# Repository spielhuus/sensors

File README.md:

# IoT Sensors

In this Project some IoT Sensors and actors are created. The goal is it to build low energy and cost efficient modules Depending

Various IoT Sensors using Wi-Fi or Lora.

# Sensor Projects

## Attiny/LoraWan Temperature and CO2 Sensor 

## Attmega328 Multi Sensor Board

The Atmega 328 Board has connector to different sesnsors. The collected data is uloaded to the things network.

Sensors
- BME280
- 

# Datasheets

- [AVR Microcontroller Hardware Design Considerations](https://www.microchip.com/wwwAppNotes/AppNotes.aspx?appnote=en591472)
- [BME280](https://ae-bst.resource.bosch.com/media/_tech/media/datasheets/BST-BME280_DS002.pdf)
- [CCS811]https://ams.com/documents/20143/36005/CCS811_AN000368_2-00.pdf/eca2b181-2937-ca92-65b5-9b43550bb20f)

# Links

- https://www.mikrocontroller.net/articles/AVR-Tutorial
- https://github.com/ClemensRiederer/TinyLoRa-BME280_v1.1
- https://learn.sparkfun.com/tutorials/ccs811-air-quality-breakout-hookup-guide
- http://www.iot-lab.org/blog/101/
- https://www.bastelgarage.ch/sparkfun-ccs811-co2-air-quality-sensor
- https://www.arduino.cc/en/uploads/Main/Arduino_Nano-Rev3.2-SCH.pdf

----

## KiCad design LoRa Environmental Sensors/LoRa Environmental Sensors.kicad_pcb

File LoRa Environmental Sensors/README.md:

# LoRa Environmental Sensors 

</img> </img> <!-- img src="https://cloud.githubusercontent.com/assets/4307137/10105284/26aa7ad4-63ae-11e5-88b7-bc523a095c9f.png" width="15%"></img> </img> </img> </img --> 

This Sensor can run of a battery and measures temperature, humidity and barometric pressure and send the data to TTN. 
The Board is using the ATmega328 processor, the Hope RFM96W Lora Module and the BME280 barometric pressure sensor. 

## BOM

The ATmega microprocessor needs an arduino bootloader. To burn a bootloader to the blank chip see [1]<table>

<tr><th style='width:640px'>Ref</th><th>Qnty</th><th>Value</th><th>Part</th><th>Datasheet</th><th>Description</th><th>Vendor</th></tr><tr><td>AE1</td><td>1</td><td>Antenna</td><td>Device:Antenna</td><td>~</td><td>Antenna symbol</td><td></td></tr><tr><td>C1, C2</td><td>2</td><td>100</td><td>Device:CP</td><td>~</td><td>Polarised capacitor</td><td></td></tr><tr><td>C3</td><td>1</td><td>22pf</td><td>Device:C</td><td>~</td><td>Unpolarized capacitor</td><td></td></tr><tr><td>C4</td><td>1</td><td>22pf </td><td>Device:C</td><td>~</td><td>Unpolarized capacitor</td><td></td></tr><tr><td>J1</td><td>1</td><td>Input</td><td>Connector:Conn_01x01_Female</td><td>~</td><td>Generic connector, single row, 01x01, script generated (kicad-library-utils/schlib/autogen/connector/)</td><td></td></tr><tr><td>J2</td><td>1</td><td>Gnd</td><td>Connector:Conn_01x01_Female</td><td>~</td><td>Generic connector, single row, 01x01, script generated (kicad-library-utils/schlib/autogen/connector/)</td><td></td></tr><tr><td>J3</td><td>1</td><td>Output</td><td>Connector:Conn_01x01_Female</td><td>~</td><td>Generic connector, single row, 01x01, script generated (kicad-library-utils/schlib/autogen/connector/)</td><td></td></tr><tr><td>J4</td><td>1</td><td>Conn_01x04</td><td>Connector_Generic:Conn_01x04</td><td>~</td><td>Generic connector, single row, 01x04, script generated (kicad-library-utils/schlib/autogen/connector/)</td><td></td></tr><tr><td>U1</td><td>1</td><td>L7805</td><td>Regulator_Linear:L7805</td><td>http://www.st.com/content/ccc/resource/technical/document/datasheet/41/4f/b3/b0/12/d4/47/88/CD00000444.pdf/files/CD00000444.pdf/jcr:content/translations/en.CD00000444.pdf</td><td>Positive 1.5A 35V Linear Regulator, Fixed Output 5V, TO-220/TO-263/TO-252</td><td></td></tr><tr><td>U2</td><td>1</td><td>ATmega328P-PU</td><td>MCU_Microchip_ATmega:ATmega328P-PU</td><td>http://ww1.microchip.com/downloads/en/DeviceDoc/ATmega328_P%20AVR%20MCU%20with%20picoPower%20Technology%20Data%20Sheet%2040001984A.pdf</td><td>20MHz, 32kB Flash, 2kB SRAM, 1kB EEPROM, DIP-28</td><td></td></tr><tr><td>U3</td><td>1</td><td>RFM95W-868S2</td><td>RF_AM_FM:RFM95W-868S2</td><td>http://www.hoperf.com/upload/rf/RFM95_96_97_98W.pdf</td><td>Low power long range transceiver module, SPI and parallel interface, 868 MHz, spreading factor 6 to12, bandwith 7.8 to 500kHz, -111 to -148 dBm, SMD-16, DIP-16</td><td></td></tr><tr><td>Y1</td><td>1</td><td>Crystal</td><td>Device:Crystal</td><td>~</td><td>Two pin crystal</td><td></td></tr><!--TABLEROW-->
</table>

## Wiring

| HopeRF RFM95 LoRa transceiver module |	ATmega8 Pin |   |	   	HopeRF RFM95 LoRa transceiver module |	ATmega8 Pin |
| ----- | ---- | --- | ---- | ---- |
| ANT |	- |   |	   	GND |	- |
| GND |	GND |   |	   	DIO5 | 	- |
| DIO3 |	- 	 |   |  	RESET |	PD5 (11) |
| DIO4 |	- 	  |   | 	NSS |	PB2 (16) |
| 3.3V |	3.3V 	|   |   	SCK |	PB5 (19) |
| DIO0 |	PD2 (4) |   | 	MOSI 7	PB3 (17) |
| DIO1 |	PD3 (5) |   | 	MISO |	PB4 (18) |
| DIO2 |	- 	  |   | 	GND |	- |

## Prepare the Arduino IDE

I asume the arduino IDE is already installed. 

Add the Libraries to you IDE:

- Within the IDE Libarary Manager Install the BME280 Library by Tyler Glenn.
- Install the lmic library as ZIP file.
  - Download the arduino-lmic library as zip file from: https://github.com/matthijskooijman/arduino-lmic
  - Install the arduino-lmic-master.zip in the Arduino IDE:
    Select menu: Sketch | Include Library | Add .Zip Library 
- Make the following changes in ./arduino-lmic-master/src/lmic/config.h:
  - If you live in Europe, set: #define CFG_eu868 1
  - If you use a HopeRF RFM95 module, set: #define CFG_sx1276_radio 1
  - If you want logging in the serial monitor, set:
    - #define LMIC_DEBUG_LEVEL 2
    - #define LMIC_FAILURE_TO Serial
  - Uncomment line: #define DISABLE_PING
    Disable this feature. It is not needed and space is freed up.
  - Uncomment line: #define DISABLE_BEACONS

    Disable this feature. It is not needed and space is freed up.

## Installation

 the armega328-sensor.ino sketarduinofile  ch from this repository into the arduino ide. 
 Edit the keys from TTN in the sketch and change the PIN-Mappings:

```
const lmic_pinmap lmic_pins = {
  .nss = 10,                       // chip select on feather (rf95module) CS
  .rxtx = LMIC_UNUSED_PIN,
  .rst = 5,                       // reset pin
  .dio = {2, 3, LMIC_UNUSED_PIN}, // assumes external jumpers [feather_lora_jumper]
```

## Payload Format

The Payload is encoded as byte array.

| byte | content |
| ---- | ------- |
| 0..1 | temperature (*100) |
| 2..3 | humidity (*100) |
| 4..8 | barometric pressure |

To decode the values add this code in the TTM Console as decoder under Paload Formats.

```
function Decoder(bytes, port) {
  temp = ((bytes[0]) << 8)
              + ((bytes[1]));
  hum = ((bytes[2]) << 8)
              + ((bytes[3]));
  pres = ((bytes[4]) << 24)
              + ((bytes[5]) << 16)
              + ((bytes[6]) << 8)
              + ((bytes[7]));

  return {
    pressure: ( pres / 100 ),
    temperature: ( temp / 100 ),
    humidity: ( hum / 100 )
  };
}
```

## Datasheets

- [ATmega328/P](http://ww1.microchip.com/downloads/en/devicedoc/atmel-42735-8-bit-avr-microcontroller-atmega328-328p_datasheet.pdf)
- [Bosch BME280](https://ae-bst.resource.bosch.com/media/_tech/media/datasheets/BST-BME280_DS002.pdf)
- [RFM95/96/97/98(W) - Low Power Long Range Transceiver Module](http://www.hoperf.com/upload/rf/RFM95_96_97_98W.pdf)

## Links

1. [TinyLoRa-BME280 v1.1](https://github.com/ClemensRiederer/TinyLoRa-BME280_v1.1)

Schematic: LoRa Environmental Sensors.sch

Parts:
BT1: Battery_Cell; BatteryHolder_Keystone_3034_1x20mm
C1, C2: 0.1uF; C_0603_1608Metric_Pad1.05x0.95mm_HandSolder
J1: SPI; PinHeader_2x03_P2.54mm_Vertical
R1, R2: 4.7k; R_0603_1608Metric_Pad1.05x0.95mm_HandSolder
U1: BME280; Bosch_LGA-8_2.5x2.5mm_P0.65mm_ClockwisePinNumbering
U2: ATtiny85-20SU; SOIJ-8_5.3x5.3mm_P1.27mm
U3: RFM95W-868S2; HOPERF_RFM9XW_SMD

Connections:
/AtTiny_Reset: J1.5, U2.1 (~RESET~/PB5)
/CS: R1.1, U1.2, U2.2 (XTAL1/PB3)
/MISO: J1.1, U1.5, U2.5 (AREF/PB0), U3.2
/MOSI: J1.4, U1.3, U2.6 (PB1), U3.3
/NSS: R2.1, U2.3 (XTAL2/PB4), U3.5
/SCK: J1.3, U1.4, U2.7 (PB2), U3.4
GND: BT1.2, C1.2, C2.2, J1.6, U1.1, U1.7, U2.4 (GND), U3.1, U3.8, U3.10
VCC: BT1.1, C1.1, C2.1, J1.2, R1.2, R2.2, U1.6, U1.8, U2.8 (VCC), U3.13

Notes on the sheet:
Power
VCC Decoupling Capacitors
SPI Interface

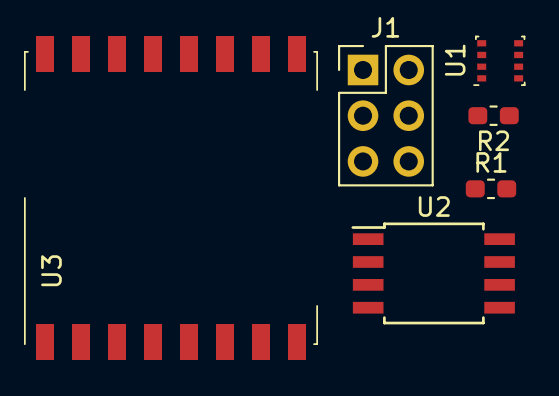
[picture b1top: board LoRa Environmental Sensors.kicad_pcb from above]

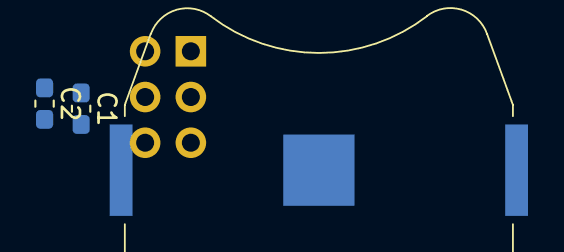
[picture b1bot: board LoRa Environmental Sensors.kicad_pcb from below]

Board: 2 copper layers, 9 parts (3 on the bottom side), 8 nets, no tracks yet.

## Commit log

2018-10-21 initial import
2018-10-21 update mega picture
2018-10-21 add bom
2018-10-26 work on project structure
2018-10-27 update redme
2018-11-11 add tiny LoRawq
2018-11-11 add Tiny LoRa
2018-11-11 update hardware
2018-11-17 update env sensor
2018-11-18 add kicad libraries

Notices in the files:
README.md:
CC BY-SA
